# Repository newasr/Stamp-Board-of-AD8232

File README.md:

# AD8232 Stamp Board - PCB Design  

This repository contains the **KiCad v9** design files for a **compact AD8232 stamp board**, built according to **Figure 66** of the [AD8232 datasheet](https://www.analog.com/media/en/technical-documentation/data-sheets/ad8232.pdf).  

## Project Overview  
The **AD8232** is an integrated signal conditioning block designed for **ECG and biopotential measurement** applications. This project involves designing a **compact and manufacturable PCB** with the following key features:  

- **Compact Form Factor** – Optimized layout for minimal space usage  
- **Standardized Terminals** – VDD, GND, LO+, LO-, OUT, nSDN, LA, RA, RL  
- **Proper Grounding** – Copper pours on top and bottom layers for improved signal integrity  
- **Manufacturing-Ready** – Includes **Gerber files, BOM, and 3D visualization**  

## Files Included  
- **Schematic** – Circuit design of the AD8232 stamp board  
- **PCB Layout** – Optimized component placement and routing  
- **PCB Routing** – Defined traces and copper pours for signal integrity  
- **Gerber Files** – Ready for PCB fabrication  
- **Bill of Materials (BOM)** – Includes Digikey part numbers and component details  
- **3D Visualization** – Ensures proper component placement and alignment  

## Tools Used  
This project was developed using **KiCad v9**, an open-source EDA tool.  

### Custom Libraries  
- **myLibrary.kicad_sym** – Custom schematic symbols  
- **myLibrary.pretty** – Custom footprints and 3D models  

### Component Footprints  
- All **resistors, capacitors, inductors, and LEDs** use:  
  **0402_1005Metric**  

---

## Schematic  

## PCB Layout  
### Component Placement  

### Overall Board Layout  

---

## 3D View  
### Top View  

### Bottom View  

---

## License  
This project is licensed under the **MIT License**. See the [LICENSE](LICENSE) file for details.  

## Contact  
Akash Sridhar – [GitHub](https://github.com/akashsridhar20)

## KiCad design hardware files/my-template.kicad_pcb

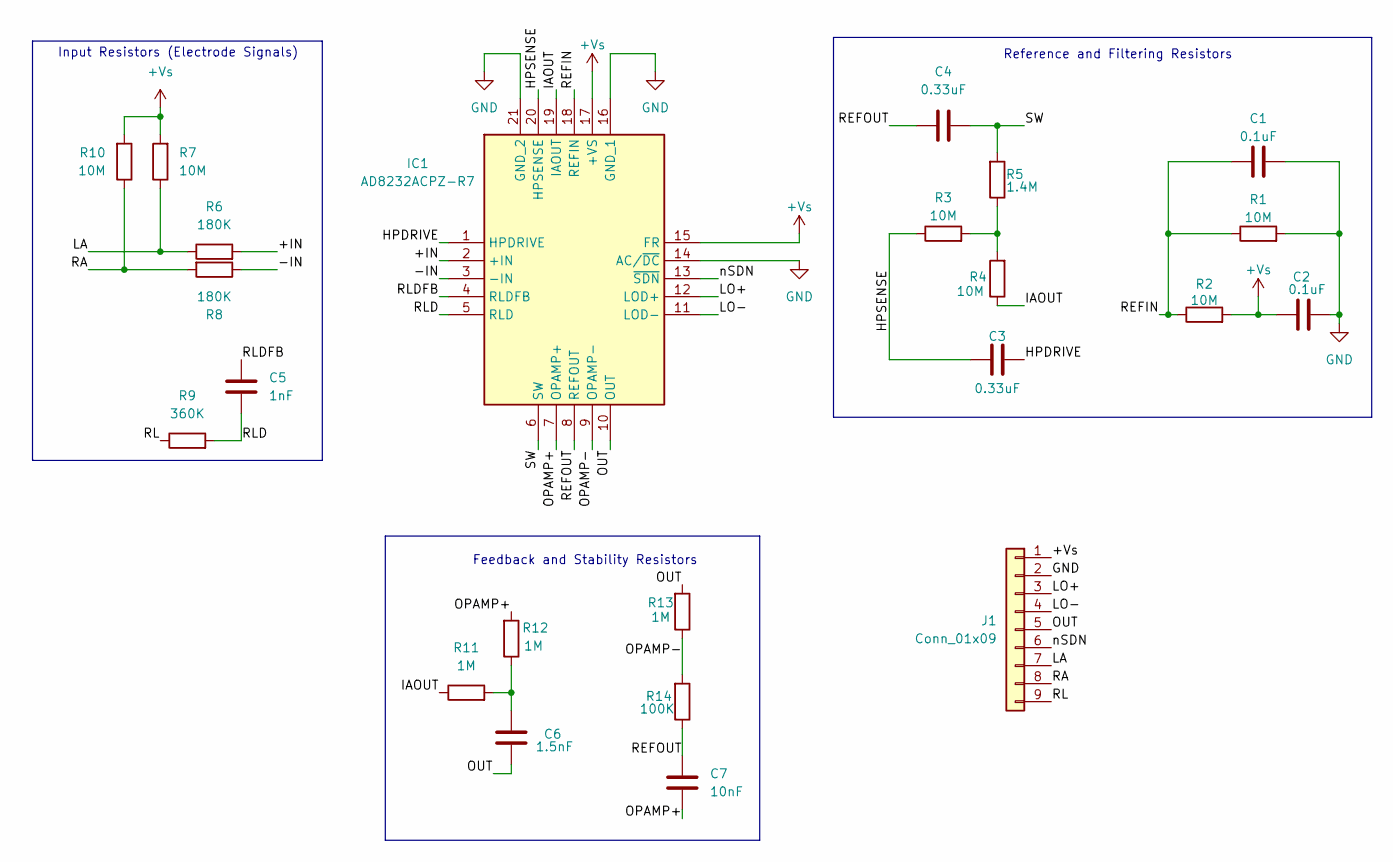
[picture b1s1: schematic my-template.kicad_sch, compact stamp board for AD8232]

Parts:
C1, C2: 0.1uF; C_0402_1005Metric; Digikey Part# 399-14871-2-ND
C3, C4: 0.33uF; C_0402_1005Metric; Digikey Part# 445-172465-2-ND
C5: 1nF; C_0402_1005Metric; Digikey Part# 399-C0402C102K9RACTUTR-ND
C6: 1.5nF; C_0402_1005Metric; Digikey Part# 478-KGM05AR70J152KHTR-ND
C7: 10nF; C_0402_1005Metric; Digikey Part# 478-KGM05AR70J103KHTR-ND
IC1: AD8232ACPZ-R7; CP_20_10_ADI; Mouser Part Number 584-AD8232ACPZ-R7
J1: Conn_01x09; PinHeader_1x09_P2.54mm_Vertical
R1, R2, R3, R4, R7, R10: 10M; R_0402_1005Metric; Digikey Part# 541-10.0MLCT-ND
R5: 1.4M; R_0402_1005Metric; Digikey Part# RMCF0402FT1M40TR-ND
R6, R8: 180K; R_0402_1005Metric; Digikey Part# CR0402-FX-1803GLFCT-ND
R9: 360K; R_0402_1005Metric; Digikey Part# P360KLTR-ND
R11, R12, R13: 1M; R_0402_1005Metric; Digikey Part# A129663CT-ND
R14: 100K; R_0402_1005Metric; Digikey Part# 311-100KLRTR-ND

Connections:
+Vs: C2.1, IC1.15 (FR), IC1.17 (+VS), J1.1, R2.2, R7.2, R10.2
/+IN: IC1.2 (+IN), R6.2
/-IN: IC1.3 (-IN), R8.1
/HPDRIVE: C3.2, IC1.1 (HPDRIVE)
/HPSENSE: C3.1, IC1.20 (HPSENSE), R3.1
/IAOUT: IC1.19 (IAOUT), R4.1, R11.1
/LA: J1.7, R6.1, R7.1
/LO+: IC1.12 (LOD+), J1.3
/LO-: IC1.11 (LOD-), J1.4
/OPAMP+: C7.2, IC1.7 (OPAMP+), R12.2
/OPAMP-: IC1.9 (OPAMP-), R13.1, R14.2
/OUT: C6.1, IC1.10 (OUT), J1.5, R13.2
/RA: J1.8, R8.2, R10.1
/REFIN: C1.1, IC1.18 (REFIN), R1.1, R2.1
/REFOUT: C4.1, C7.1, IC1.8 (REFOUT), R14.1
/RL: J1.9, R9.1
/RLD: C5.2, IC1.5 (RLD), R9.2
/RLDFB: C5.1, IC1.4 (RLDFB)
/SW: C4.2, IC1.6 (SW), R5.2
/nSDN: IC1.13 (~SDN), J1.6
GND: C1.2, C2.2, IC1.14 (AC/~DC), IC1.16 (GND_1), IC1.21 (GND_2), J1.2, R1.2
unnamed: C6.2, R11.2, R12.1
unnamed: R3.2, R4.2, R5.1

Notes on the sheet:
Feedback and Stability Resistors
Input Resistors (Electrode Signals)
Reference and Filtering Resistors

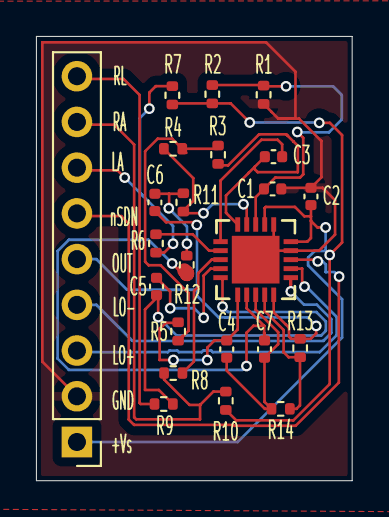
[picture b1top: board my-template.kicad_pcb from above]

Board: 2 copper layers, 17.5 x 24.7 mm, 23 parts (0 on the bottom side), 23 nets.

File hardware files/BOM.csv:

"Reference","Value","Footprint","Qty","Digikey Part#","Digikey URL"
"IC1","AD8232ACPZ-R7","myLibrary:CP_20_10_ADI","1","505-AD8232ACPZ-R7CT-ND","https://www.digikey.in/en/products/detail/analog-devices-inc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"
"R14","100K","Resistor_SMD:R_0402_1005Metric","1","311-100KLRTR-ND","https://www.digikey.in/en/products/detail/yageo/RC0402FR-071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"
"R11,R12,R13","1M","Resistor_SMD:R_0402_1005Metric","3","A129663CT-ND","https://www.digikey.in/en/products/detail/te-connectivity-pa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"
"R9","360K","Resistor_SMD:R_0402_1005Metric","1","P360KLTR-ND","https://www.digikey.in/en/products/detail/panasonic-electron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"
"R6,R8","180K","Resistor_SMD:R_0402_1005Metric","2","CR0402-FX-1803GLFCT-ND","https://www.digikey.in/en/products/detail/bourns-inc/CR0402-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"
"R5","1.4M","Resistor_SMD:R_0402_1005Metric","1","RMCF0402FT1M40TR-ND","https://www.digikey.in/en/products/detail/stackpole-electron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"
"R1,R2,R3,R4,R7,R10","10M","Resistor_SMD:R_0402_1005Metric","6","541-10.0MLCT-ND","https://www.digikey.in/en/products/detail/vishay-dale/CRCW04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"
"J1","Conn_01x09","Connector_PinHeader_2.54mm:PinHeader_1x09_P2.54mm_Vertical","1","",""
"C7","10nF","Capacitor_SMD:C_0402_1005Metric","1","478-KGM05AR70J103KHTR-ND","https://www.digikey.in/en/products/detail/kyocera-avx/KGM05A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"
"C6","1.5nF","Capacitor_SMD:C_0402_1005Metric","1","478-KGM05AR70J152KHTR-ND","https://www.digikey.in/en/products/detail/kyocera-avx/KGM05A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"
"C5","1nF","Capacitor_SMD:C_0402_1005Metric","1","399-C0402C102K9RACTUTR-ND","https://www.digikey.in/en/products/detail/kemet/C0402C102K9R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"
"C3,C4","0.33uF","Capacitor_SMD:C_0402_1005Metric","2","445-172465-2-ND","https://www.digikey.in/en/products/detail/tdk-corporation/C1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"
"C1,C2","0.1uF","Capacitor_SMD:C_0402_1005Metric","2","399-14871-2-ND","https://www.digikey.in/en/products/detail/kemet/C0402C104K7P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"

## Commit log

2025-03-22 added project details
2025-03-22 removed emojis
2025-03-22 added images of pcb, schematic
2025-03-22 added bom and 3d models
2025-03-22 added gerber and its zip
2025-03-22 added hardware files
2025-03-22 organised hardware files
2025-03-22 ADDED LABELS 3D IMAGE
2025-03-22 update labels in pcb
2025-03-22 Created LICENSE
